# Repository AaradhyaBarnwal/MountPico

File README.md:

# MountPico
I have created a custom RP2040 development board with awesome graphics and two header for each GPIO pins. I took inspiration from "Nimsdai", created a mountain graphics with Nimsdai's famous quote "Giving up is not in the blood" on one side and a rocket travelling across space on the other side. I also added 2 header pins for each pin, so it will be easier to check the signals and connect two components to the same pin at the same time.
Why have I design this? Why not? It looks cool! and I learnt some of KiCad on the go.

### Image of PCB

## BOM
|Comment                    |Designator                      |Footprint                                  |JLCPCB Part #|
|---------------------------|--------------------------------|-------------------------------------------|-------------|
|33pF                       |C14,C15                         |0402                                       |C1562        |
|1uF                        |C1,C9                           |0402                                       |C52923       |
|1K                         |R5,R7                           |0402                                       |C11702       |
|0.1uF                      |C10,C11,C16,C2,C3,C4,C5,C6,C7,C8|0402                                       |C1525        |
|5.1K                       |R1,R2                           |0402                                       |C25905       |
|10K                        |R6                              |0402                                       |C25744       |
|NCP1117-3.3_SOT223         |U2                              |SOT-223-3_TabPin2                          |C26537       |
|100                        |R8                              |0402                                       |C25076       |
|LED                        |D1                              |0805                                       |C84256       |
|RP2040                     |U1                              |QFN-56-1EP_7x7mm_P0.4mm_EP3.2x3.2mm        |C2040        |
|27                         |R3,R4                           |0402                                       |C25100       |
|W25Q128JVS                 |U3                              |Winbond_USON-8-1EP_3x2mm_P0.5mm_EP0.2x1.6mm|C2843335     |
|12MHz                      |Y1                              |Crystal_SMD_3225-4Pin_3.2x2.5mm            |C481407      |
|USB_C_Receptacle_USB2.0_14P|J1                              |USB_C_Receptacle_HRO_TYPE-C-31-M-12        |C165948      |
|10uF                       |C12,C13                         |0603                                       |C19702       |
|SW_Push                    |SW1                             |SW_Push_SPST_NO_Alps_SKRK                  |C720477      |
|                           |                                |                                           |             |
|                           |Vendor                          |Price                                      |             |
|PCB Manufacturing          |JLCPCB                          |$4.00                                      |             |
|PCBA                       |JLCPCB                          |$48.08                                     |             |
|Shipping                   |                                |$22.99                                     |             |

## How to use 
Solder the PCB headers and then you can use it as a raspberry pi pico

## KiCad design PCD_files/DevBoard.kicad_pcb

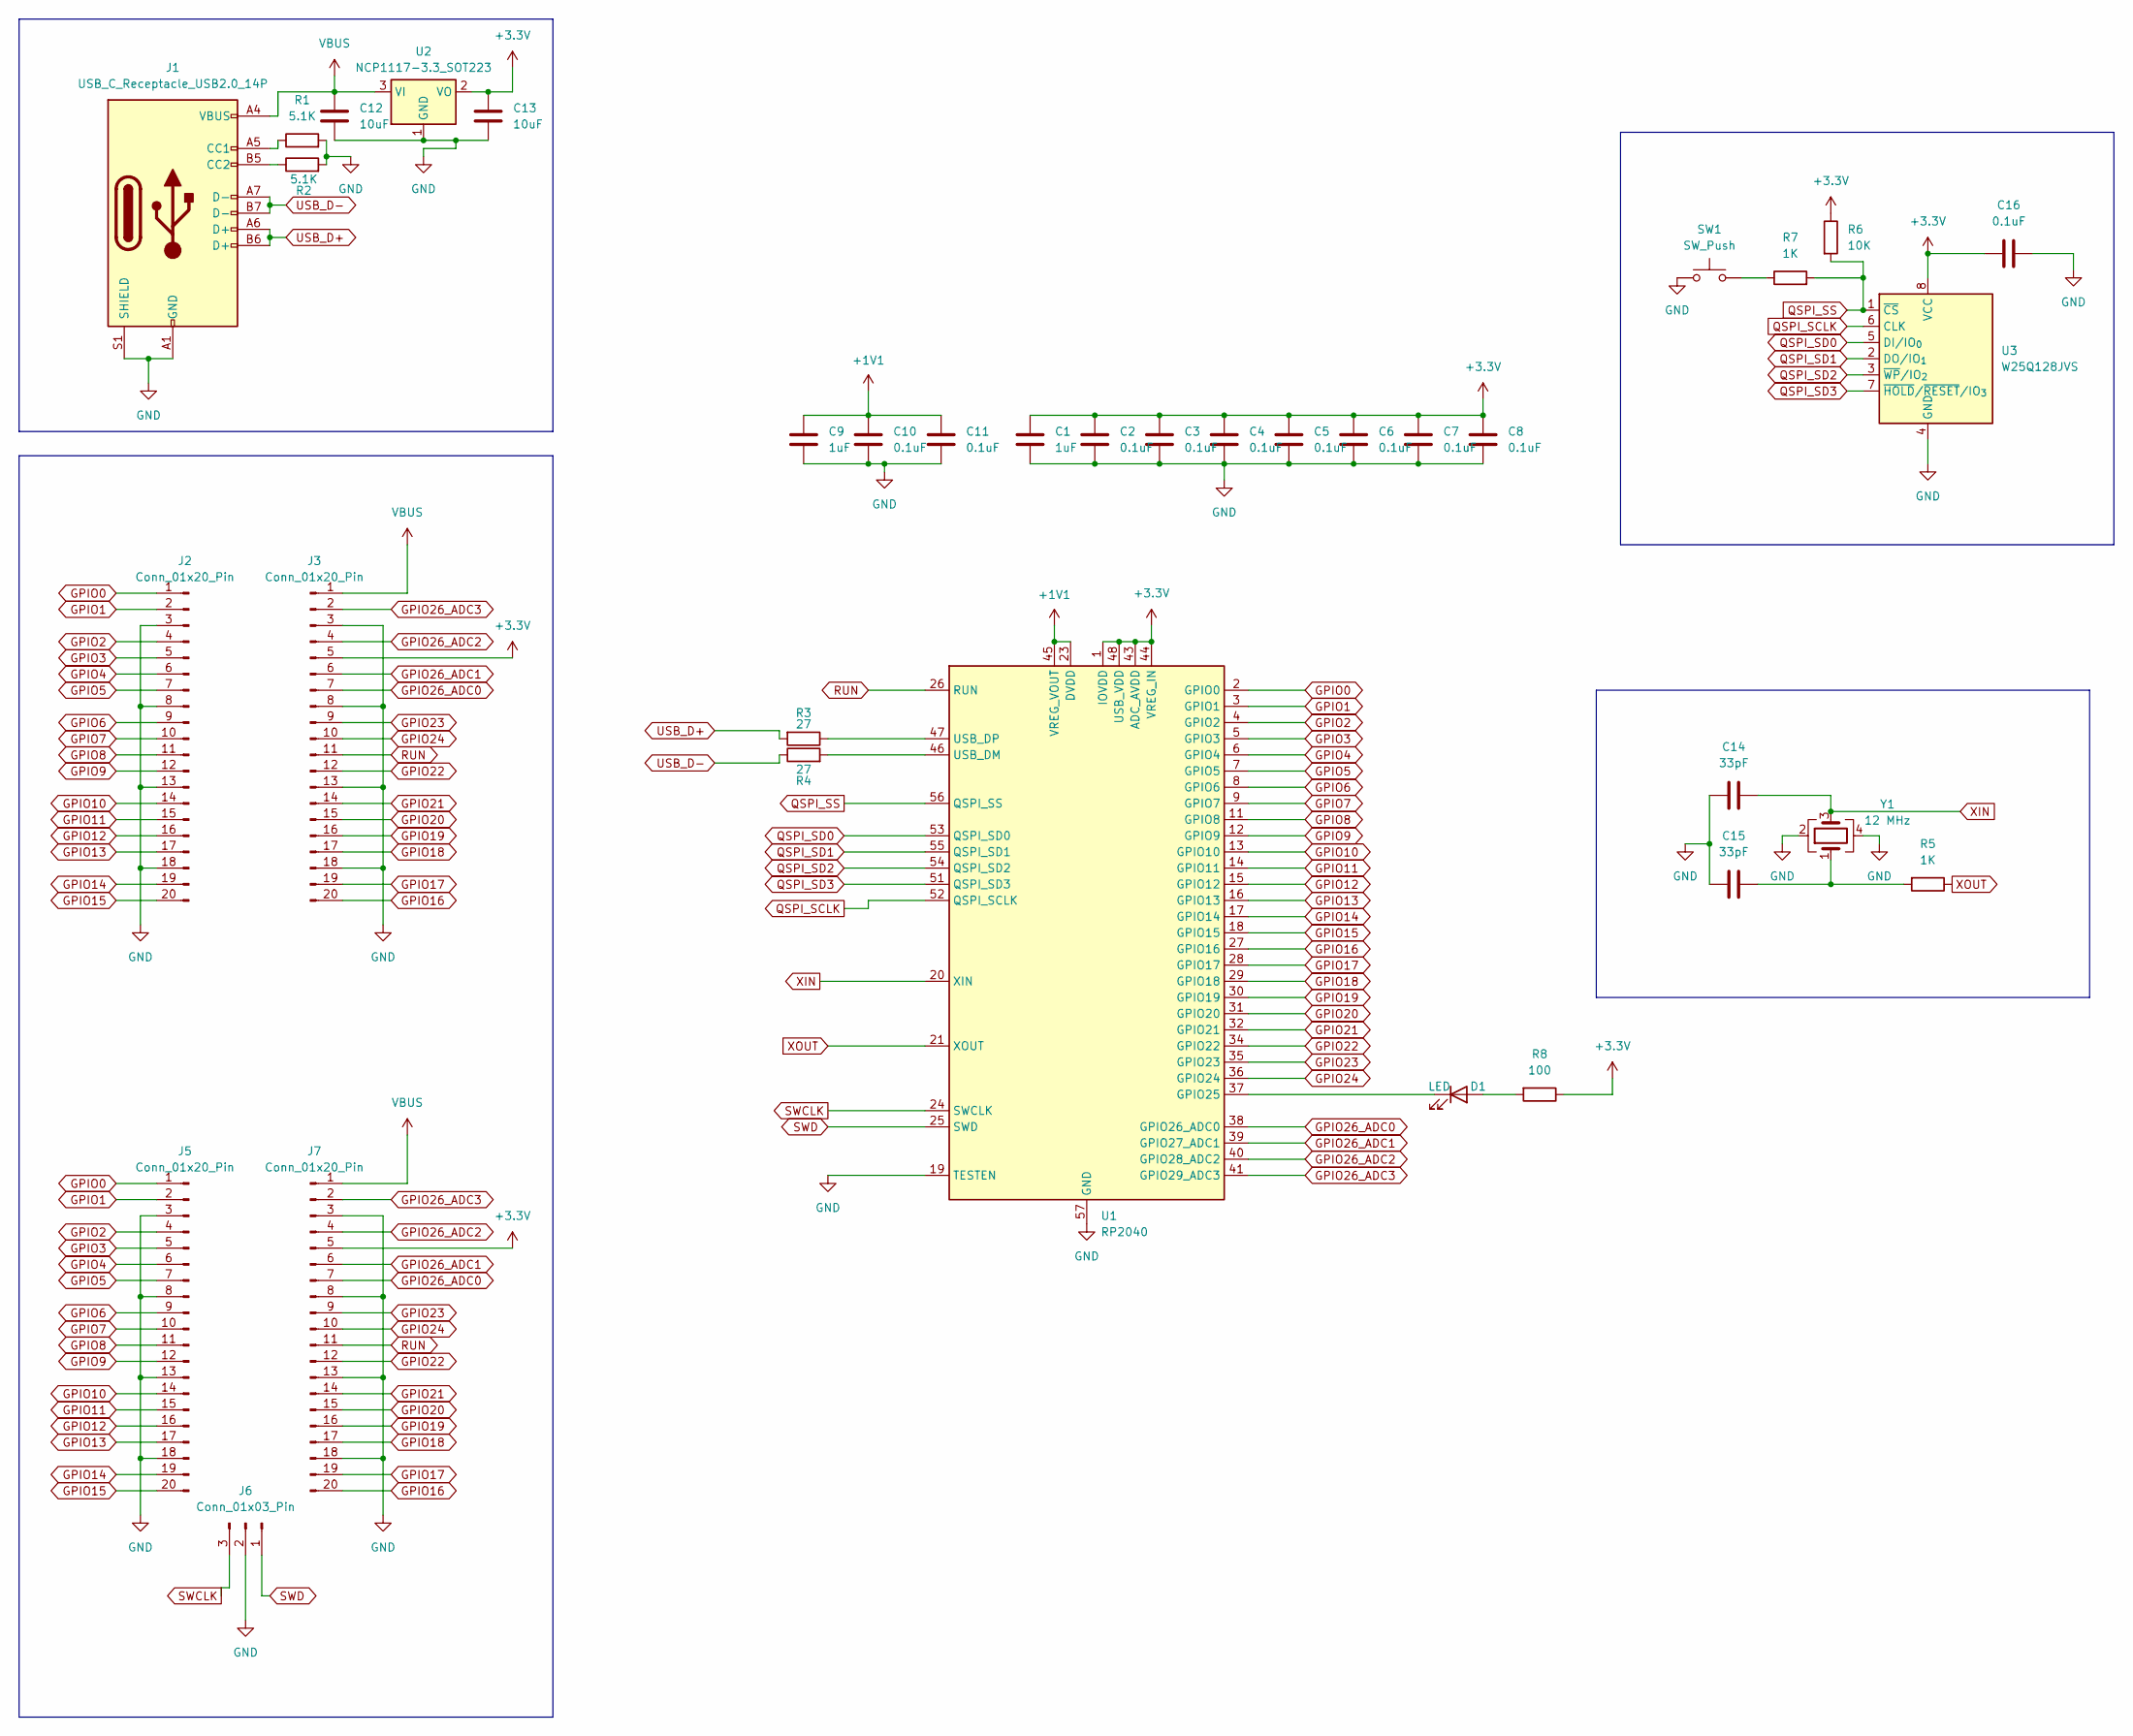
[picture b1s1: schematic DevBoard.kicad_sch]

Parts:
C1, C9: 1uF; C_0402_1005Metric
C2, C3, C4, C5, C6, C7, C8, C10, C11, C16: 0.1uF; C_0402_1005Metric
C12, C13: 10uF; C_0603_1608Metric
C14, C15: 33pF; C_0402_1005Metric
D1: LED; LED_0805_2012Metric
J1: USB_C_Receptacle_USB2.0_14P; USB_C_Receptacle_HRO_TYPE-C-31-M-12
J2, J3, J5, J7: Conn_01x20_Pin; PinHeader_1x20_P2.54mm_Vertical
J6: Conn_01x03_Pin; PinHeader_1x03_P2.54mm_Vertical
R1, R2: 5.1K; R_0402_1005Metric
R3, R4: 27; R_0402_1005Metric
R5, R7: 1K; R_0402_1005Metric
R6: 10K; R_0402_1005Metric
R8: 100; R_0402_1005Metric_Pad0.72x0.64mm_HandSolder
SW1: SW_Push; SW_Push_SPST_NO_Alps_SKRK
U1: RP2040; QFN-56-1EP_7x7mm_P0.4mm_EP3.2x3.2mm
U2: NCP1117-3.3_SOT223; SOT-223-3_TabPin2
U3: W25Q128JVS; Winbond_USON-8-1EP_3x2mm_P0.5mm_EP0.2x1.6mm
Y1: 12 MHz; Crystal_SMD_3225-4Pin_3.2x2.5mm

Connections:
+1V1: C9.1, C10.1, C11.1, U1.23 (DVDD), U1.45 (VREG_VOUT), U1.50 (DVDD)
+3.3V: C1.1, C2.1, C3.1, C4.1, C5.1, C6.1, C7.1, C8.1, C13.1, C16.2, J3.5, J7.5, R6.1, R8.1, U1.1 (IOVDD), U1.10 (IOVDD), U1.22 (IOVDD), U1.33 (IOVDD), U1.42 (IOVDD), U1.43 (ADC_AVDD), U1.44 (VREG_IN), U1.48 (USB_VDD), U1.49 (IOVDD), U2.2 (VO), U3.8 (VCC)
GND: C1.2, C2.2, C3.2, C4.2, C5.2, C6.2, C7.2, C8.2, C9.2, C10.2, C11.2, C12.2, C13.2, C14.2, C15.2, C16.1, J1.A1 (GND), J1.A12 (GND), J1.B1 (GND), J1.B12 (GND), J1.S1 (SHIELD), J2.3, J2.8, J2.13, J2.18, J3.3, J3.8, J3.13, J3.18, J5.3, J5.8, J5.13, J5.18, J6.2, J7.3, J7.8, J7.13, J7.18, R1.2, R2.2, SW1.1, U1.19 (TESTEN), U1.57 (GND), U2.1 (GND), U3.4 (GND), Y1.2, Y1.4
GPIO0: J2.1, J5.1, U1.2 (GPIO0)
GPIO1: J2.2, J5.2, U1.3 (GPIO1)
GPIO2: J2.4, J5.4, U1.4 (GPIO2)
GPIO3: J2.5, J5.5, U1.5 (GPIO3)
GPIO4: J2.6, J5.6, U1.6 (GPIO4)
GPIO5: J2.7, J5.7, U1.7 (GPIO5)
GPIO6: J2.9, J5.9, U1.8 (GPIO6)
GPIO7: J2.10, J5.10, U1.9 (GPIO7)
GPIO8: J2.11, J5.11, U1.11 (GPIO8)
GPIO9: J2.12, J5.12, U1.12 (GPIO9)
GPIO10: J2.14, J5.14, U1.13 (GPIO10)
GPIO11: J2.15, J5.15, U1.14 (GPIO11)
GPIO12: J2.16, J5.16, U1.15 (GPIO12)
GPIO13: J2.17, J5.17, U1.16 (GPIO13)
GPIO14: J2.19, J5.19, U1.17 (GPIO14)
GPIO15: J2.20, J5.20, U1.18 (GPIO15)
GPIO16: J3.20, J7.20, U1.27 (GPIO16)
GPIO17: J3.19, J7.19, U1.28 (GPIO17)
GPIO18: J3.17, J7.17, U1.29 (GPIO18)
GPIO19: J3.16, J7.16, U1.30 (GPIO19)
GPIO20: J3.15, J7.15, U1.31 (GPIO20)
GPIO21: J3.14, J7.14, U1.32 (GPIO21)
GPIO22: J3.12, J7.12, U1.34 (GPIO22)
GPIO23: J3.9, J7.9, U1.35 (GPIO23)
GPIO24: J3.10, J7.10, U1.36 (GPIO24)
GPIO26_ADC0: J3.7, J7.7, U1.38 (GPIO26_ADC0)
GPIO26_ADC1: J3.6, J7.6, U1.39 (GPIO27_ADC1)
GPIO26_ADC2: J3.4, J7.4, U1.40 (GPIO28_ADC2)
GPIO26_ADC3: J3.2, J7.2, U1.41 (GPIO29_ADC3)
unnamed: C15.1, R5.2, Y1.1
unnamed: D1.2 (A), R8.2
unnamed: D1.1 (K), U1.37 (GPIO25)
unnamed: J1.A5 (CC1), R1.1
unnamed: J1.B5 (CC2), R2.1
unnamed: R7.1, SW1.2
unnamed: R4.2, U1.46 (USB_DM)
unnamed: R3.1, U1.47 (USB_DP)
QSPI_SCLK: U1.52 (QSPI_SCLK), U3.6 (CLK)
QSPI_SD0: U1.53 (QSPI_SD0), U3.5 (DI/IO_{0})
QSPI_SD1: U1.55 (QSPI_SD1), U3.2 (DO/IO_{1})
QSPI_SD2: U1.54 (QSPI_SD2), U3.3 (~WP/IO_{2})
QSPI_SD3: U1.51 (QSPI_SD3), U3.7 (~HOLD/~RESET/IO_{3})
QSPI_SS: R6.2, R7.2, U1.56 (QSPI_SS), U3.1 (~CS)
RUN: J3.11, J7.11, U1.26 (RUN)
SWCLK: J6.3, U1.24 (SWCLK)
SWD: J6.1, U1.25 (SWD)
USB_D+: J1.A6 (D+), J1.B6 (D+), R3.2
USB_D-: J1.A7 (D-), J1.B7 (D-), R4.1
VBUS: C12.1, J1.A4 (VBUS), J1.A9 (VBUS), J1.B4 (VBUS), J1.B9 (VBUS), J3.1, J7.1, U2.3 (VI)
XIN: C14.1, U1.20 (XIN), Y1.3
XOUT: R5.1, U1.21 (XOUT)

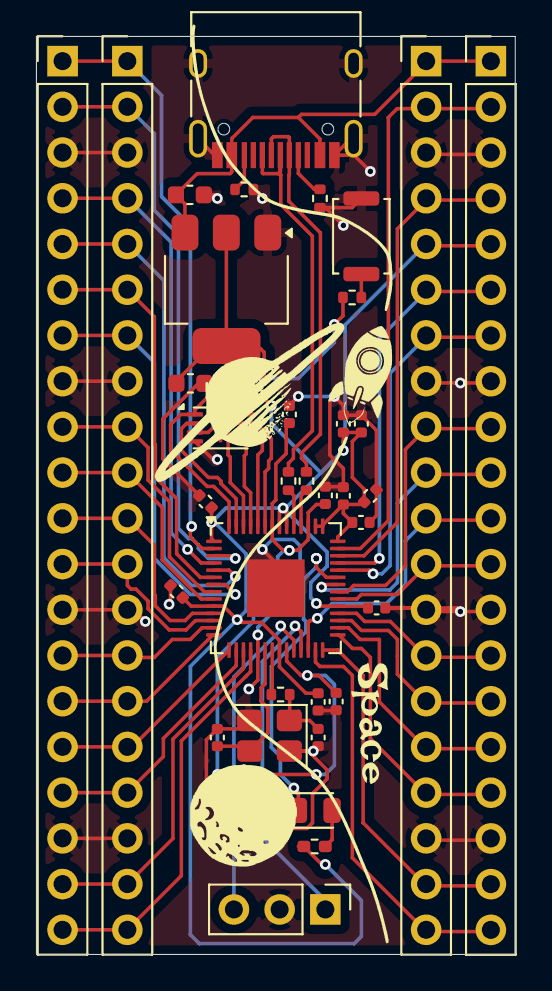
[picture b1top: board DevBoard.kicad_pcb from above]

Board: 2 copper layers, 26.6 x 51.0 mm, 38 parts (1 on the bottom side), 54 nets.

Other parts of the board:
 : LOGO
 #2: LOGO

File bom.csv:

Designator,Footprint,Quantity,Value,LCSC Part #
"C1, C9",0402,2,1uF,
"C10, C11, C16, C2, C3, C4, C5, C6, C7, C8",0402,10,0.1uF,
"C12, C13",0603,2,10uF,
"C14, C15",0402,2,33pF,
D1,0805,1,LED,
J1,USB_C_Receptacle_HRO_TYPE-C-31-M-12,1,USB_C_Receptacle_USB2.0_14P,
"J2, J3, J5, J7",PinHeader_1x20_P2.54mm_Vertical,4,Conn_01x20_Pin,
J6,PinHeader_1x03_P2.54mm_Vertical,1,Conn_01x03_Pin,
"R1, R2",0402,2,5.1K,
"R3, R4",0402,2,27,
"R5, R7",0402,2,1K,
R6,0402,1,10K,
R8,0402,1,100,
SW1,SW_Push_SPST_NO_Alps_SKRK,1,SW_Push,
U1,QFN-56-1EP_7x7mm_P0.4mm_EP3.2x3.2mm,1,RP2040,
U2,SOT-223-3_TabPin2,1,NCP1117-3.3_SOT223,
U3,Winbond_USON-8-1EP_3x2mm_P0.5mm_EP0.2x1.6mm,1,W25Q128JVS,
Y1,Crystal_SMD_3225-4Pin_3.2x2.5mm,1,12 MHz,
